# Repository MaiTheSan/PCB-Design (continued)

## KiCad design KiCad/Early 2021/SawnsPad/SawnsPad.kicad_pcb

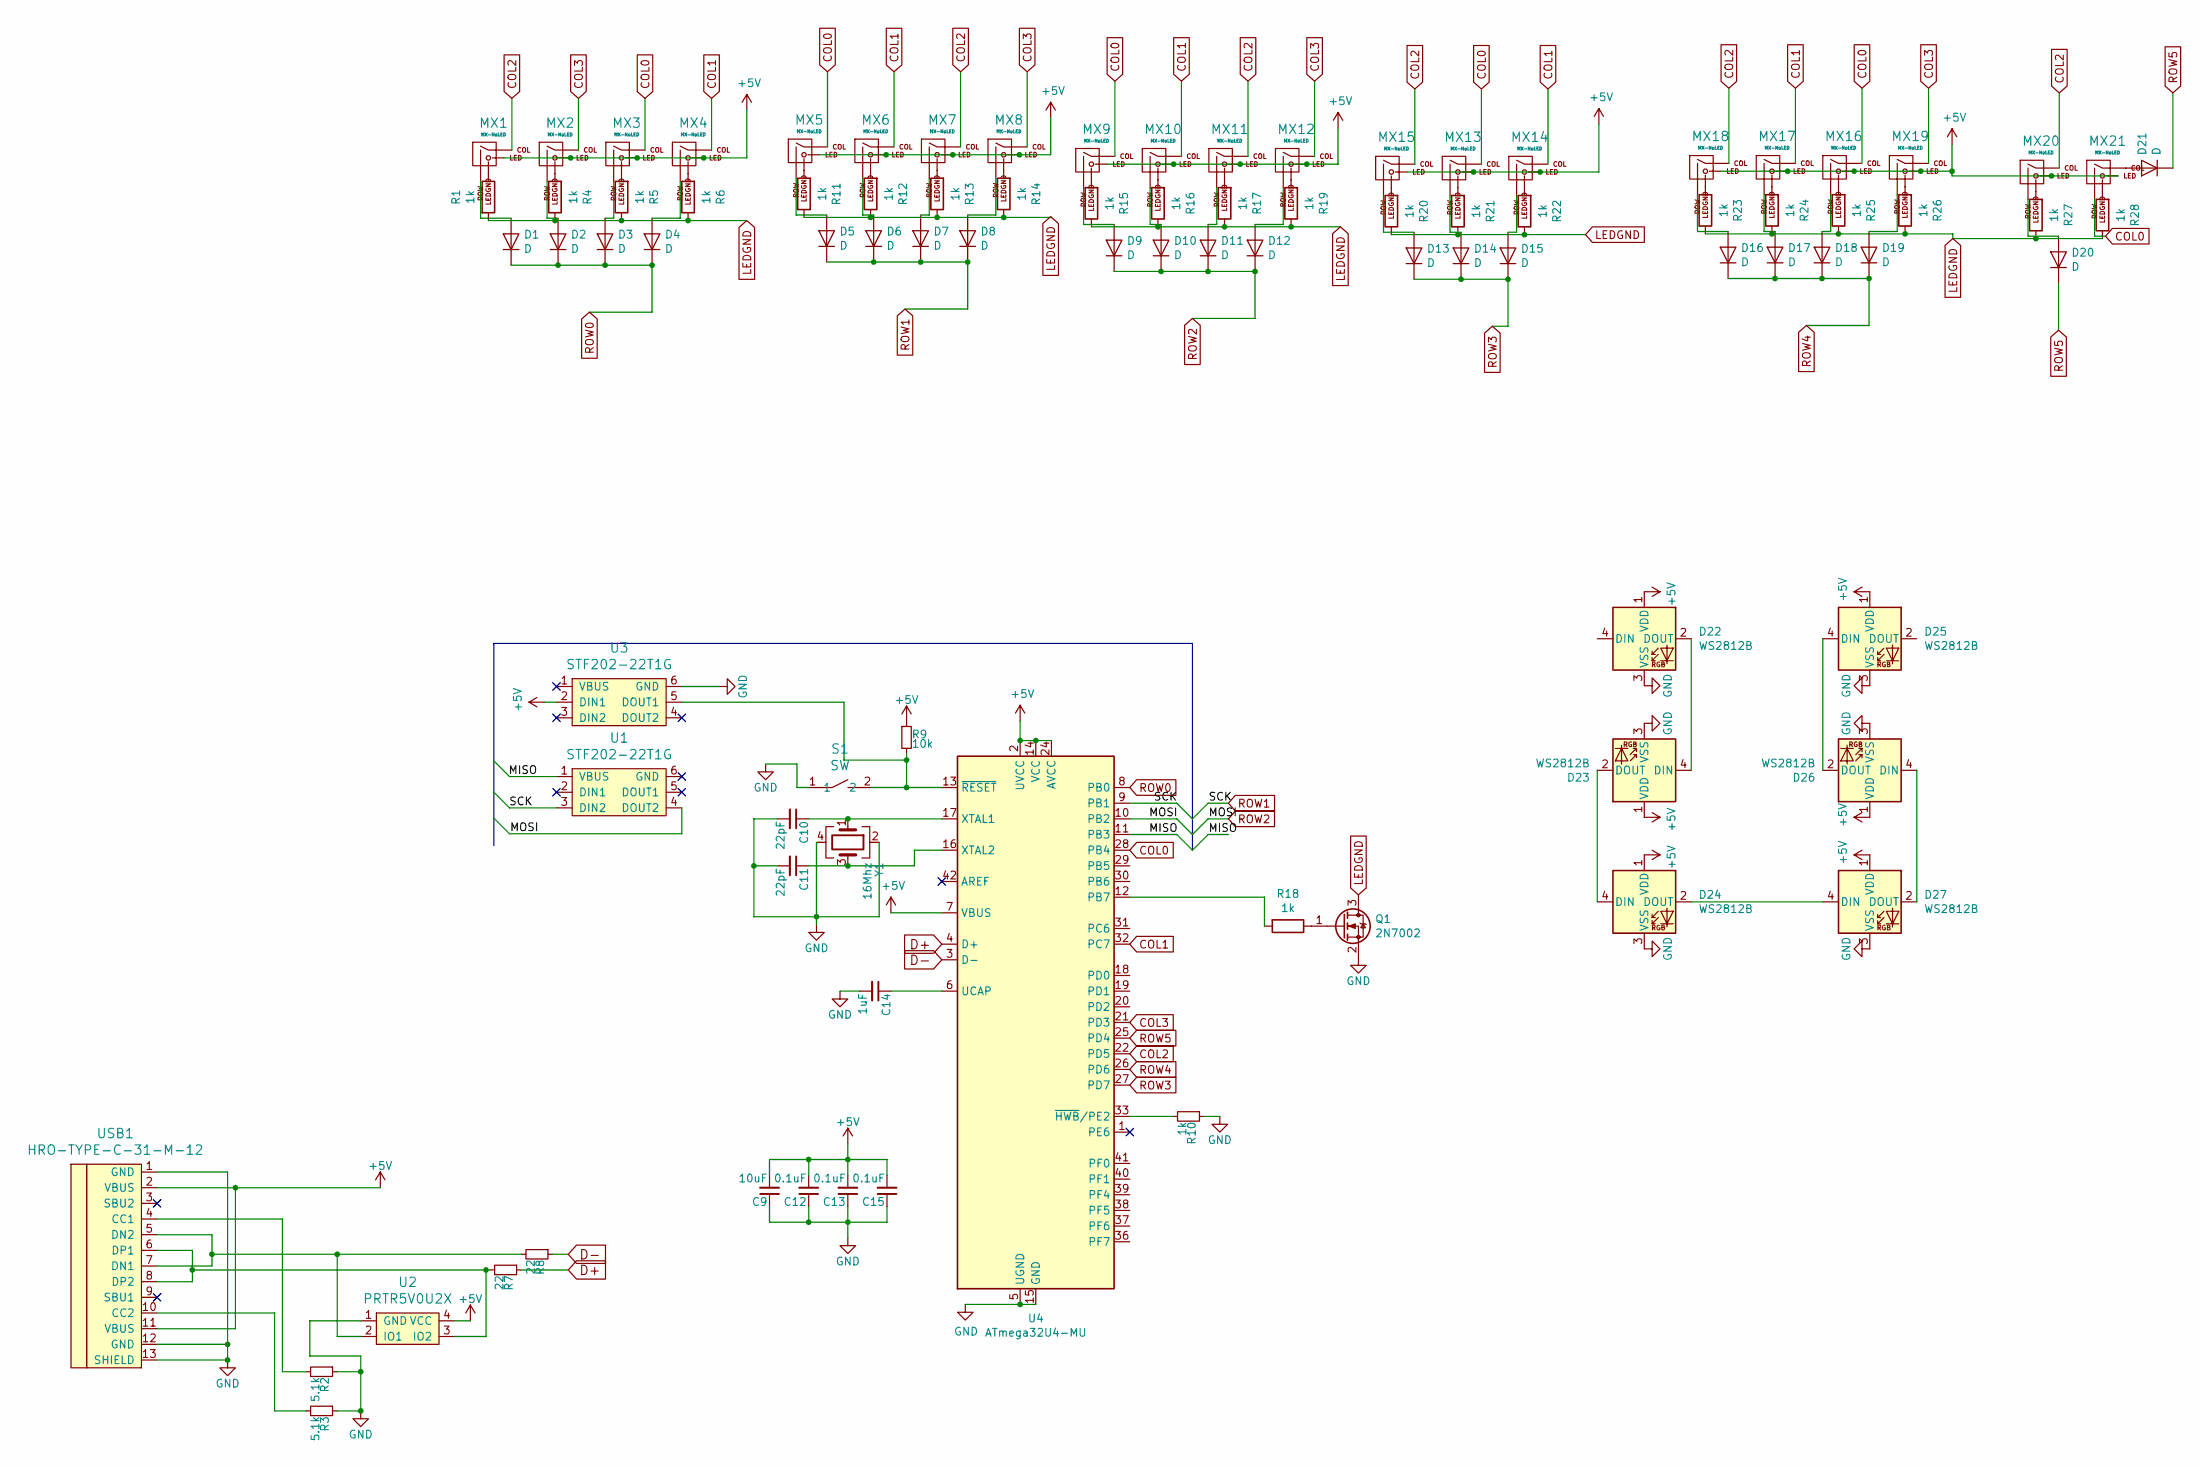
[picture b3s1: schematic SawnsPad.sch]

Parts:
C9: 10uF; SMD-0402
C10, C11: 22pF; SMD-0402
C12, C13, C15: 0.1uF; SMD-0402
C14: 1uF; SMD-0402
D1, D2, D3, D4, D5, D6, D7, D8, D9, D10, D11, D12, D13, D14, D15, D16, D17, D18, D19, D20, D21: D; D_SOD-123
D22, D23, D24, D25, D26, D27: WS2812B; LED_WS2812B_PLCC4_5.0x5.0mm_P3.2mm
MX1, MX3, MX5, MX7, MX9, MX11, MX13, MX15, MX16, MX18: MX-NoLED; MXOnly-1U-FLIPPED
MX2, MX4, MX6, MX8, MX10, MX14, MX17, MX20: MX-NoLED; MXOnly-1U
MX12: MX-NoLED; MXOnly-2U
MX19, MX21: MX-NoLED; MXOnly-2U-FLIPPED
Q1: 2N7002; SOT-23
R1, R4, R5, R6, R10, R11, R12, R13, R14, R15, R16, R17, R18, R19, R20, R21, R22, R23, R24, R25, R26, R27, R28: 1k; R_0805
R2, R3: 5.1k; R_0805
R7, R8: 22; R_0805
R9: 10k; R_0805
S1: SW; SKQG-1155865
U1, U3: STF202-22T1G; Reset_Pretty
U2: PRTR5V0U2X; SOT143B
U4: ATmega32U4-MU; QFN-44-1EP_7x7mm_P0.5mm_EP5.2x5.2mm
USB1: HRO-TYPE-C-31-M-12; HRO-TYPE-C-31-M-12-Assembly
Y1: 16Mhz; Crystal_SMD_3225-4Pin_3.2x2.5mm

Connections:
+5V: C9.2, C12.2, C13.2, C15.2, D22.1 (VDD), D23.1 (VDD), D24.1 (VDD), D25.1 (VDD), D26.1 (VDD), D27.1 (VDD), MX1.3 (LED), MX2.3 (LED), MX3.3 (LED), MX4.3 (LED), MX5.3 (LED), MX6.3 (LED), MX7.3 (LED), MX8.3 (LED), MX9.3 (LED), MX10.3 (LED), MX11.3 (LED), MX12.3 (LED), MX13.3 (LED), MX14.3 (LED), MX15.3 (LED), MX16.3 (LED), MX17.3 (LED), MX18.3 (LED), MX19.3 (LED), MX20.3 (LED), MX21.3 (LED), R9.1, U2.4 (VCC), U3.2 (DIN1), U4.2 (UVCC), U4.7 (VBUS), U4.14 (VCC), U4.24 (AVCC), U4.34 (VCC), U4.44 (AVCC), USB1.2 (VBUS), USB1.11 (VBUS)
/MISO: U1.1 (VBUS), U4.11 (PB3)
COL0: MX3.1 (COL), MX5.1 (COL), MX9.1 (COL), MX13.1 (COL), MX16.1 (COL), MX21.2 (ROW), U4.28 (PB4)
COL1: MX4.1 (COL), MX6.1 (COL), MX10.1 (COL), MX14.1 (COL), MX17.1 (COL), U4.32 (PC7)
COL2: MX1.1 (COL), MX7.1 (COL), MX11.1 (COL), MX15.1 (COL), MX18.1 (COL), MX20.1 (COL), U4.22 (PD5)
COL3: MX2.1 (COL), MX8.1 (COL), MX12.1 (COL), MX19.1 (COL), U4.21 (PD3)
D+: R7.1, U4.4 (D+)
D-: R8.1, U4.3 (D-)
GND: C9.1, C10.2, C11.2, C12.1, C13.1, C14.2, C15.1, D22.3 (VSS), D23.3 (VSS), D24.3 (VSS), D25.3 (VSS), D26.3 (VSS), D27.3 (VSS), Q1.2 (S), R2.1, R3.1, R10.1, S1.1, U2.1 (GND), U3.6 (GND), U4.5 (UGND), U4.15 (GND), U4.23 (GND), U4.35 (GND), U4.43 (GND), U4.45 (GND), USB1.1 (GND), USB1.12 (GND), USB1.13 (SHIELD), Y1.2, Y1.4
LEDGND: Q1.3 (D), R1.2, R4.1, R5.1, R6.1, R11.1, R12.1, R13.1, R14.1, R15.1, R16.1, R17.1, R19.1, R20.1, R21.1, R22.1, R23.1, R24.1, R25.1, R26.1, R27.1, R28.1
unnamed: C10.1, U4.17 (XTAL1), Y1.1
unnamed: C11.1, U4.16 (XTAL2), Y1.3
unnamed: C14.1, U4.6 (UCAP)
unnamed: D1.2 (A), MX1.2 (ROW)
unnamed: D2.2 (A), MX2.2 (ROW)
unnamed: D3.2 (A), MX3.2 (ROW)
unnamed: D4.2 (A), MX4.2 (ROW)
unnamed: D5.2 (A), MX5.2 (ROW)
unnamed: D6.2 (A), MX6.2 (ROW)
unnamed: D7.2 (A), MX7.2 (ROW)
unnamed: D8.2 (A), MX8.2 (ROW)
unnamed: D9.2 (A), MX9.2 (ROW)
unnamed: D10.2 (A), MX10.2 (ROW)
unnamed: D11.2 (A), MX11.2 (ROW)
unnamed: D12.2 (A), MX12.2 (ROW)
unnamed: D13.2 (A), MX15.2 (ROW)
unnamed: D14.2 (A), MX13.2 (ROW)
unnamed: D15.2 (A), MX14.2 (ROW)
unnamed: D16.2 (A), MX18.2 (ROW)
unnamed: D17.2 (A), MX17.2 (ROW)
unnamed: D18.2 (A), MX16.2 (ROW)
unnamed: D19.2 (A), MX19.2 (ROW)
unnamed: D20.2 (A), MX20.2 (ROW)
unnamed: D21.2 (A), MX21.1 (COL)
unnamed: D22.2 (DOUT), D23.4 (DIN)
unnamed: D23.2 (DOUT), D24.4 (DIN)
unnamed: D24.2 (DOUT), D27.4 (DIN)
unnamed: D25.4 (DIN), D26.2 (DOUT)
unnamed: D26.4 (DIN), D27.2 (DOUT)
unnamed: MX1.4 (LEDGND), R1.1
unnamed: MX2.4 (LEDGND), R4.2
unnamed: MX3.4 (LEDGND), R5.2
unnamed: MX4.4 (LEDGND), R6.2
unnamed: MX5.4 (LEDGND), R11.2
unnamed: MX6.4 (LEDGND), R12.2
unnamed: MX7.4 (LEDGND), R13.2
unnamed: MX8.4 (LEDGND), R14.2
unnamed: MX9.4 (LEDGND), R15.2
unnamed: MX10.4 (LEDGND), R16.2
unnamed: MX11.4 (LEDGND), R17.2
unnamed: MX12.4 (LEDGND), R19.2
unnamed: MX13.4 (LEDGND), R21.2
unnamed: MX14.4 (LEDGND), R22.2
unnamed: MX15.4 (LEDGND), R20.2
unnamed: MX16.4 (LEDGND), R25.2
unnamed: MX17.4 (LEDGND), R24.2
unnamed: MX18.4 (LEDGND), R23.2
unnamed: MX19.4 (LEDGND), R26.2
unnamed: MX20.4 (LEDGND), R27.2
unnamed: MX21.4 (LEDGND), R28.2
unnamed: Q1.1 (G), R18.1
unnamed: R2.2, USB1.4 (CC1)
unnamed: R3.2, USB1.10 (CC2)
unnamed: R7.2, U2.3 (IO2), USB1.6 (DP1), USB1.8 (DP2)
unnamed: R8.2, U2.2 (IO1), USB1.5 (DN2), USB1.7 (DN1)
unnamed: R9.2, S1.2, U3.5 (DOUT1), U4.13 (~RESET)
unnamed: R10.2, U4.33 (~HWB~/PE2)
unnamed: R18.2, U4.12 (PB7)
ROW0: D1.1 (K), D2.1 (K), D3.1 (K), D4.1 (K), U4.8 (PB0)
ROW1: D5.1 (K), D6.1 (K), D7.1 (K), D8.1 (K), U1.3 (DIN2), U4.9 (PB1)
ROW2: D9.1 (K), D10.1 (K), D11.1 (K), D12.1 (K), U1.4 (DOUT2), U4.10 (PB2)
ROW3: D13.1 (K), D14.1 (K), D15.1 (K), U4.27 (PD7)
ROW4: D16.1 (K), D17.1 (K), D18.1 (K), D19.1 (K), U4.26 (PD6)
ROW5: D20.1 (K), D21.1 (K), U4.25 (PD4)

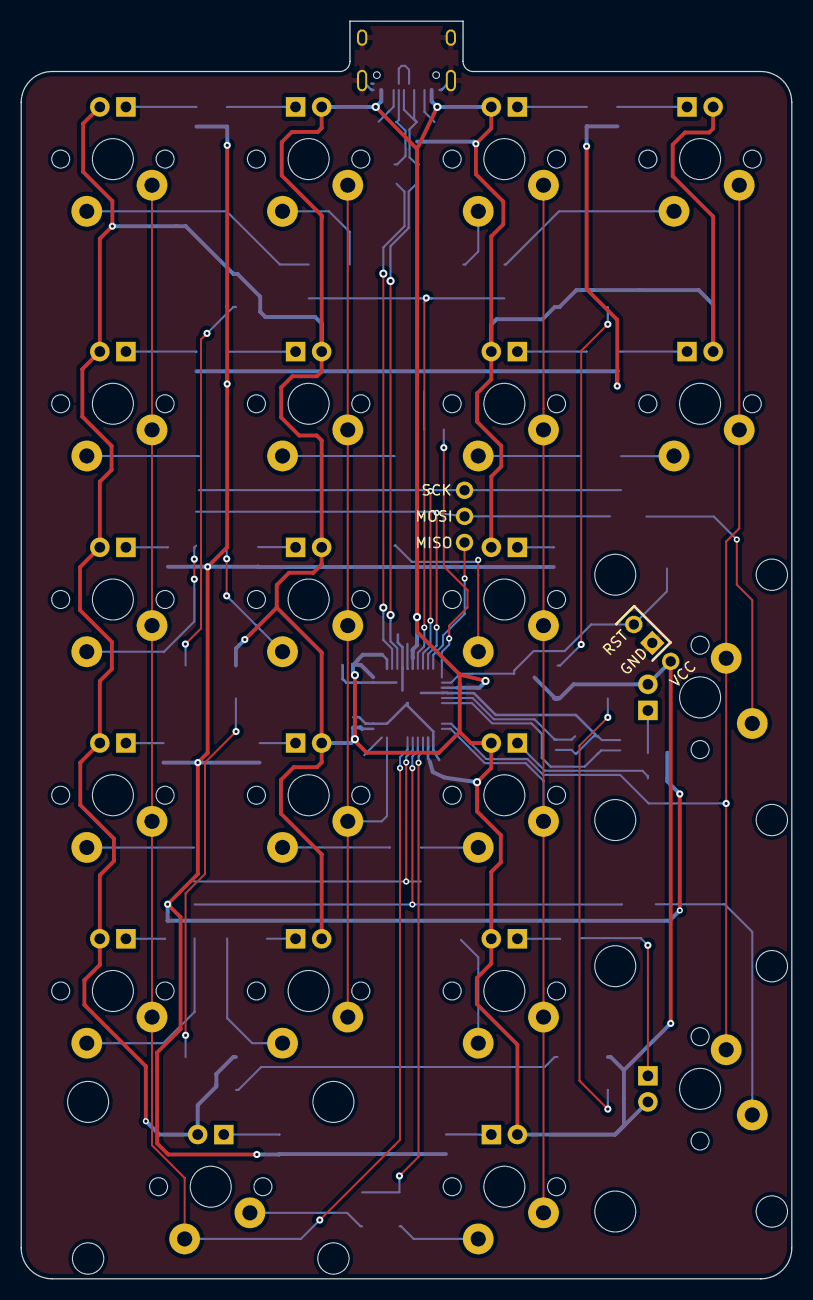
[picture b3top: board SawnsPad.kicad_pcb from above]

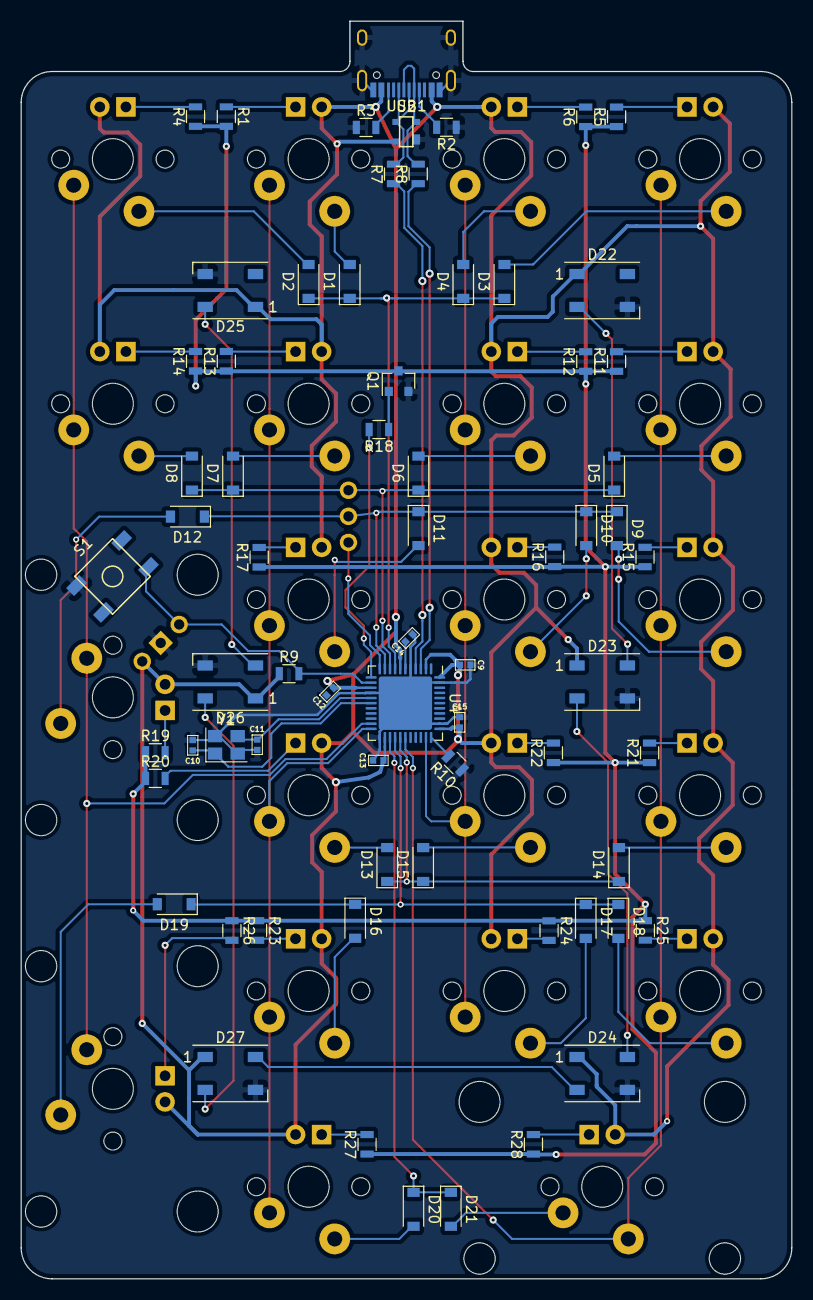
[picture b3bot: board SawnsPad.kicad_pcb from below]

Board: 2 copper layers, 75.0 x 122.4 mm, 91 parts (68 on the bottom side), 74 nets.

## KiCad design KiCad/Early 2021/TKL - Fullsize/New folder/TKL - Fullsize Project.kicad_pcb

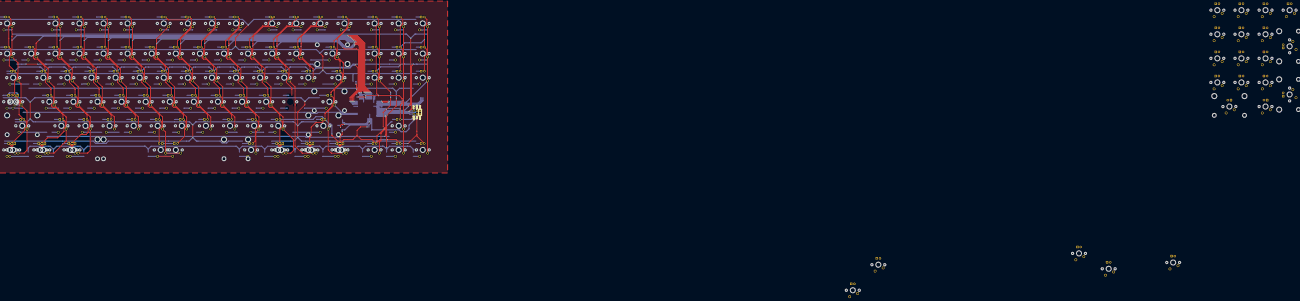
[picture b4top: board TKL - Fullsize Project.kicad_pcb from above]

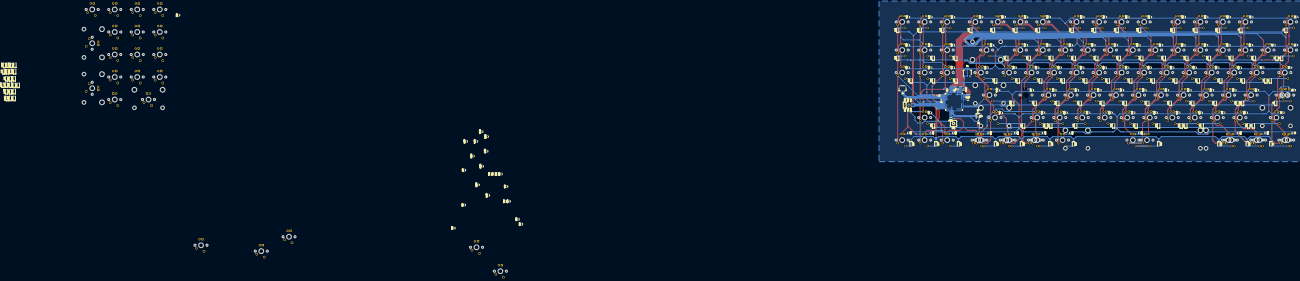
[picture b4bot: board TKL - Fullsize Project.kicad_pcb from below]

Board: 2 copper layers, 351 parts (233 on the bottom side), 257 nets.

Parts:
C2, C5: 1uF; C_0603
C3, C4: 22pF; C_0603
C6, C7, C8: 0.1uF; C_0603
D1, D2, D3, D4, D5, D6, D7, D8, D9, D10, D11, D12, D13, D14, D15, D16, D17, D18, D19, D20, D21, D22, D23, D24, D25, D26, D27, D28, D29, D30, D31, D32, D33, D34, D35, D36, D37, D38, D39, D40, D41, D42, D43, D44, D45, D46, D47, D48, D49, D50, D51, D52, D53, D54, D55, D56, D57, D58, D59, D60, D61, D62, D63, D64, D65, D66, D67, D68, D69, D70, D71, D72, D73, D74, D75, D76, D77, D78, D79, D80, D81, D82, D83, D84, D85, D86, D87, D88, D89, D90, D91, D92, D93, D94, D95, D96, D97, D98, D99, D100, D101, D102, D103, D104, D105, D106, D107, D108, D110: SOD-123; D_SOD-123-Pretty
J1: AVR-ISP-6; Reset_Pretty-Mask
J2: SM04B-SRSS-TB(LF)(SN); JST-SR-4
K_0: MX 2U; MXOnly-2U-FLIPPED
K_0x1, K_1, K_2, K_3, K_4, K_5, K_6, K_7, K_8, K_9: MX 1U; MXOnly-1U
K_': MXOnly-1U
K_*1: MX 1U; MXOnly-1U
K_+1: MX 1U; MXOnly-1U
K_+2: MX 2U; MXOnly-2U
K_-1, K_-2: MX 1U; MXOnly-1U
K_/1: MX 1U; MXOnly-1U
K_/?/1: MX 1U; MXOnly-1U
K_:;1: MX 1U; MXOnly-1U
K_<1: MX 1U; MXOnly-1U
K_>1: MX 1U; MXOnly-1U
K_A1: MX 1U; MXOnly-1U
K_B1: MX 1U; MXOnly-1U
K_BkSp1: MX 2U; MXOnly-2U-ReversedStabilizers
K_C1: MX 1U; MXOnly-1U
K_CapLk1: MX 1.25U; MXOnly-1.25U
K_CapLk2: MX 1.75U; MXOnly-1.75U-FLIPPED
K_D1: MX 1U; MXOnly-1U
K_Del1: MX 1U; MXOnly-1U-FLIPPED
K_Delete1: MX 1U; MXOnly-1U
K_Down1: MX 1U; MXOnly-1U
K_E1: MX 1U; MXOnly-1U
K_ESC1: MX 1U; MXOnly-1U
K_End1: MX 1U; MXOnly-1U
K_Enter1: MX 2.25U; MXOnly-2.25U
K_Enter2: MX 2U; MXOnly-2U
K_F1, K_F2, K_F3, K_F4, K_F5, K_F6, K_F7, K_F8, K_F9, K_F10, K_F11, K_F12, K_F13: MX 1U; MXOnly-1U
K_FN5: MX 1.25U; MXOnly-1.25U-FLIPPED
K_Fn1, K_Fn2, K_Fn3, K_Fn4: MX 1U; MXOnly-1U
K_G1: MX 1U; MXOnly-1U
K_H1: MX 1U; MXOnly-1U
K_Home1: MX 1U; MXOnly-1U
K_I1: MX 1U; MXOnly-1U
K_Ins1: MX 1U; MXOnly-1U
K_J1: MX 1U; MXOnly-1U
K_K1: MX 1U; MXOnly-1U
K_L1: MX 1U; MXOnly-1U
K_Left1: MX 1U; MXOnly-1U
K_LeftAlt1: MX 1.25U; MXOnly-1.25U
K_LeftAlt2: MX 1.5U; MXOnly-1.5U-FLIPPED
K_LeftControl1: MX 1.25U; MXOnly-1.25U
K_LeftControl2: MX 1.5U; MXOnly-1.5U-FLIPPED
K_LeftShift1: MX 2.25U; MXOnly-2.25U
K_LeftWin1: MX 1.25U; MXOnly-1.25U
K_LeftWin2: MX 1U; MXOnly-1U-FLIPPED
K_M1: MX 1U; MXOnly-1U
K_Menu1: MX 1.25U; MXOnly-1.25U-FLIPPED
K_N1: MX 1U; MXOnly-1U
K_Num1, K_Num2, K_Num3, K_Num4, K_Num5, K_Num6, K_Num7, K_Num8, K_Num9: MX 1U; MXOnly-1U
K_NumLk1: MX 1U; MXOnly-1U
K_O1: MX 1U; MXOnly-1U
K_P1: MX 1U; MXOnly-1U
K_Pause1: MX 1U; MXOnly-1U
K_PgDn1: MX 1U; MXOnly-1U
K_PgUp1: MX 1U; MXOnly-1U
K_PrtSc1: MX 1U; MXOnly-1U
K_Q1: MX 1U; MXOnly-1U
K_R1: MX 1U; MXOnly-1U
K_Right1: MX 1U; MXOnly-1U
K_RightAlt1: MX 1.25U; MXOnly-1.25U
K_RightAltx1: MX 1.5U; MXOnly-1.5U
K_RightControl1: MX 1.25U; MXOnly-1.25U-FLIPPED
K_RightFN1: MX 1.5U; MXOnly-1.5U
K_RightShift1: MX 2.75U; MXOnly-2.75U
K_Rightwinx1: MX 1U; MXOnly-1U
K_S1: MX 1U; MXOnly-1U
K_ScLk1: MX 1U; MXOnly-1U
K_Sleep1: MX 1U; MXOnly-1U
K_Space1: MX 6.25U; MXOnly-6.25U-FLIPPED
K_Space2: MX 7U; MXOnly-7U
K_T1: MX 1U; MXOnly-1U
K_Tab1: MX 1.5U; MXOnly-1.5U
K_U1: MX 1U; MXOnly-1U
K_Up1: MX 1U; MXOnly-1U
K_V1: MX 1U; MXOnly-1U
K_W1: MX 1U; MXOnly-1U
K_X1: MX 1U; MXOnly-1U
K_Y1: MX 1U; MXOnly-1U
K_Z1: MX 1U; MXOnly-1U
K_[{1: MX 1U; MXOnly-1U
K_\|1: MX 1.5U; MXOnly-1.5U
K_`1: MX 1U; MXOnly-1U
K_}]1: MX 1U; MXOnly-1U
Q1: DSS60601MZ4-13; SOT-223-3_TabPin2
R1, R2, R3, R4, R5, R6, R7, R8, R9, R10, R11, R12, R13, R14, R15, R16, R17, R18, R19, R20, R21, R22, R23, R24, R25, R26, R27, R28, R29, R30, R31, R32, R33, R34, R35, R36, R37, R38, R39, R40, R41, R42, R43, R44, R45, R46, R47, R48, R49, R50, R51, R52, R53, R54, R55, R56, R57, R58, R59, R60, R61, R62, R63, R64, R65, R66, R67, R68, R69, R70, R71, R72, R73, R74, R75, R76, R77, R78, R79, R80, R81, R82, R83, R84, R85, R86, R87, R89, R90, R91, R92, R93, R94, R95, R96, R97, R98, R99, R100, R101, R102, R103, R104, R105, R106, R107, R108, R111, R113: 1k; R_0805
R88: 300; R_0805
R109: 1.5k; R_0805
R112: 10k; R_0805
SW1: SW_Push; SKQG-1155865
U2: AT90USB1286-AU; TQFP-64_14x14mm_P0.8mm
Y1: 16MHz; Crystal_SMD_3225-4Pin_3.2x2.5mm

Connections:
+5V: C5.2, C6.2, C7.2, C8.2, J1.2, J2.1, K_0.3, K_0x1.3, K_1.3, K_2.3, K_3.3, K_4.3, K_5.3, K_6.3, K_7.3, K_8.3, K_9.3, K_*1.3, K_+1.3, K_+2.3, K_-1.3, K_-2.3, K_/1.3, K_/?/1.3, K_:;1.3, K_<1.3, K_>1.3, K_A1.3, K_B1.3, K_BkSp1.3, K_C1.3, K_CapLk1.3, K_CapLk2.3, K_D1.3, K_Del1.3, K_Delete1.3, K_Down1.3, K_E1.3, K_ESC1.3, K_End1.3, K_Enter1.3, K_Enter2.3, K_F1.3, K_F2.3, K_F3.3, K_F4.3, K_F5.3, K_F6.3, K_F7.3, K_F8.3, K_F9.3, K_F10.3, K_F11.3, K_F12.3, K_F13.3, K_FN5.3, K_Fn1.3, K_Fn2.3, K_Fn3.3, K_Fn4.3, K_G1.3, K_H1.3, K_Home1.3, K_I1.3, K_Ins1.3, K_J1.3, K_K1.3, K_L1.3, K_Left1.3, K_LeftAlt1.3, K_LeftAlt2.3, K_LeftControl1.3, K_LeftControl2.3, K_LeftShift1.3, K_LeftWin1.3, K_LeftWin2.3, K_M1.3, K_Menu1.3, K_N1.3, K_Num1.3, K_Num2.3, K_Num3.3, K_Num4.3, K_Num5.3, K_Num6.3, K_Num7.3, K_Num8.3, K_Num9.3, K_NumLk1.3, K_O1.3, K_P1.3, K_Pause1.3, K_PgDn1.3, K_PgUp1.3, K_PrtSc1.3, K_Q1.3, K_R1.3, K_Right1.3, K_RightAlt1.3, K_RightAltx1.3, K_RightControl1.3, K_RightFN1.3, K_RightShift1.3, K_Rightwinx1.3, K_S1.3, K_ScLk1.3, K_Sleep1.3, K_Space1.3, K_Space2.3, K_T1.3, K_Tab1.3, K_U1.3, K_Up1.3, K_V1.3, K_W1.3, K_X1.3, K_Y1.3, K_Z1.3, K_[{1.3, K_\|1.3, K_`1.3, K_}]1.3, R112.1, U2.3, U2.8, U2.21, U2.52, U2.64
Col0: K_CapLk1.1, K_CapLk2.1, K_ESC1.1, K_LeftControl1.1, K_LeftControl2.1, K_LeftShift1.1, K_Tab1.1, K_`1.1, U2.61
Col1: K_1.1, K_A1.1, K_LeftWin1.1, K_LeftWin2.1, K_Q1.1, K_Z1.1, U2.60
Col2: K_2.1, K_F1.1, K_LeftAlt1.1, K_LeftAlt2.1, K_S1.1, K_W1.1, K_X1.1, U2.59
Col3: K_3.1, K_C1.1, K_D1.1, K_E1.1, K_F2.1, U2.58
Col4: K_4.1, K_F3.1, K_F13.1, K_R1.1, K_V1.1, U2.57
Col5: K_5.1, K_B1.1, K_F4.1, K_G1.1, K_Space1.1, K_Space2.1, K_T1.1, U2.56
Col6: K_6.1, K_F5.1, K_H1.1, K_N1.1, K_Y1.1, U2.51
Col7: K_7.1, K_F6.1, K_J1.1, K_M1.1, K_U1.1, U2.50
Col8: K_8.1, K_<1.1, K_F7.1, K_I1.1, K_K1.1, U2.49
Col9: K_9.1, K_>1.1, K_F8.1, K_L1.1, K_O1.1, K_RightAlt1.1, U2.48
Col10: K_0x1.1, K_/?/1.1, K_:;1.1, K_F9.1, K_FN5.1, K_P1.1, K_RightFN1.1, U2.47
Col11: K_-1.1, K_F10.1, K_Menu1.1, K_Rightwinx1.1, K_[{1.1, U2.46
Col12: K_+1.1, K_F11.1, K_Sleep1.1, K_}]1.1, U2.45
Col13: K_BkSp1.1, K_Enter1.1, K_F12.1, K_RightAltx1.1, K_RightControl1.1, K_RightShift1.1, K_\|1.1, U2.36
Col14: K_Delete1.1, K_Ins1.1, K_Left1.1, K_PrtSc1.1, U2.9
Col15: K_Down1.1, K_End1.1, K_Home1.1, K_ScLk1.1, K_Up1.1, U2.1
Col16: K_Pause1.1, K_PgDn1.1, K_PgUp1.1, K_Right1.1, U2.2
Col17: K_Fn1.1, K_Num1.1, K_Num4.1, K_Num7.1, K_NumLk1.1
Col18: K_0.1, K_/1.1, K_Fn2.1, K_Num2.1, K_Num5.1, K_Num8.1
Col19: K_*1.1, K_Del1.1, K_Fn3.1, K_Num3.1, K_Num6.1, K_Num9.1
Col20: K_+2.1, K_-2.1, K_Enter2.1, K_Fn4.1
D+: J2.3, U2.5
D-: J2.2, U2.4
GND: C2.2, C3.2, C4.2, C5.1, C6.1, C7.1, C8.1, J1.6, J2.4, Q1.3, R113.2, SW1.1, U2.6, U2.22, U2.53, U2.63, Y1.2, Y1.4
LedGND: Q1.2, R1.1, R2.1, R3.1, R4.1, R5.1, R6.1, R7.1, R8.1, R9.1, R10.1, R11.1, R12.1, R13.1, R14.1, R15.1, R16.1, R17.1, R18.1, R19.1, R20.1, R21.1, R22.1, R23.1, R24.1, R25.1, R26.1, R27.1, R28.1, R29.1, R30.1, R31.1, R32.1, R33.1, R34.1, R35.1, R36.1, R37.1, R38.1, R39.1, R40.1, R41.1, R42.1, R43.1, R44.1, R45.1, R46.1, R47.1, R48.1, R49.1, R50.1, R51.1, R52.1, R53.1, R54.1, R55.1, R56.1, R57.1, R58.1, R59.1, R60.1, R61.1, R62.1, R63.1, R64.1, R65.1, R66.1, R67.1, R68.1, R69.1, R70.1, R71.1, R72.1, R73.1, R74.1, R75.1, R76.1, R77.1, R78.1, R79.1, R80.1, R81.1, R82.1, R83.1, R84.1, R85.1, R86.1, R87.1, R89.1, R90.1, R91.1, R92.1, R93.1, R94.1, R95.1, R96.1, R97.1, R98.1, R99.1, R100.1, R101.1, R102.1, R103.1, R104.1, R105.1, R106.1, R107.1, R108.1, R111.1
MISO: J1.1, U2.13
MOSI: J1.4, U2.12
unnamed: C2.1, U2.7
unnamed: D1.2, K_ESC1.2
unnamed: D2.2, K_`1.2
unnamed: D3.2, K_Tab1.2
unnamed: D4.2, K_CapLk1.2, K_CapLk2.2
unnamed: D5.2, K_LeftShift1.2
unnamed: D6.2, K_LeftControl1.2, K_LeftControl2.2
unnamed: D7.2, K_F1.2
unnamed: D8.2, K_1.2
unnamed: D9.2, K_Q1.2
unnamed: D10.2, K_A1.2
unnamed: D11.2, K_Z1.2
unnamed: D12.2, K_LeftWin1.2, K_LeftWin2.2
unnamed: D13.2, K_F2.2
unnamed: D14.2, K_2.2
unnamed: D15.2, K_W1.2
unnamed: D16.2, K_S1.2
unnamed: D17.2, K_X1.2
unnamed: D18.2, K_LeftAlt1.2, K_LeftAlt2.2
unnamed: D19.2, K_F3.2
unnamed: D20.2, K_3.2
unnamed: D21.2, K_E1.2
unnamed: D22.2, K_D1.2
unnamed: D23.2, K_C1.2
unnamed: D24.2, K_RightAltx1.2, K_RightControl1.2
unnamed: D25.2, K_F4.2
unnamed: D26.2, K_4.2
unnamed: D27.2, K_R1.2
unnamed: D28.2, K_F13.2
unnamed: D29.2, K_V1.2
unnamed: D30.2, K_F5.2
unnamed: D31.2, K_5.2
unnamed: D32.2, K_T1.2
unnamed: D33.2, K_G1.2
unnamed: D34.2, K_B1.2
unnamed: D35.2, K_Space1.2, K_Space2.2
unnamed: D36.2, K_F6.2
unnamed: D37.2, K_6.2
unnamed: D38.2, K_Y1.2
unnamed: D39.2, K_H1.2
unnamed: D40.2, K_N1.2
unnamed: D41.2, K_F7.2
unnamed: D42.2, K_7.2
unnamed: D43.2, K_U1.2
unnamed: D44.2, K_J1.2
unnamed: D45.2, K_M1.2
unnamed: D46.2, K_F8.2
unnamed: D47.2, K_8.2
unnamed: D48.2, K_I1.2
unnamed: D49.2, K_K1.2
unnamed: D50.2, K_<1.2
unnamed: D51.2, K_RightAlt1.2
unnamed: D52.2, K_F9.2
unnamed: D53.2, K_9.2
unnamed: D54.2, K_O1.2
unnamed: D55.2, K_L1.2
unnamed: D56.2, K_>1.2
unnamed: D57.2, K_FN5.2, K_RightFN1.2
unnamed: D58.2, K_F10.2
unnamed: D59.2, K_0x1.2
unnamed: D60.2, K_P1.2
unnamed: D61.2, K_:;1.2
unnamed: D62.2, K_/?/1.2
unnamed: D63.2, K_Menu1.2, K_Rightwinx1.2
unnamed: D64.2, K_F11.2
unnamed: D65.2, K_-1.2
unnamed: D66.2, K_[{1.2
unnamed: D68.2, K_RightShift1.2
unnamed: D69.2, K_F12.2
unnamed: D70.2, K_+1.2
unnamed: D71.2, K_}]1.2
unnamed: D72.2, K_Sleep1.2
unnamed: D73.2, K_BkSp1.2
unnamed: D74.2, K_\|1.2
unnamed: D75.2, K_PrtSc1.2
unnamed: D76.2, K_Ins1.2
unnamed: D77.2, K_Delete1.2
unnamed: D78.2, K_Left1.2
unnamed: D79.2, K_ScLk1.2
unnamed: D80.2, K_Home1.2
unnamed: D81.2, K_End1.2
unnamed: D82.2, K_Up1.2
unnamed: D83.2, K_Down1.2
unnamed: D84.2, K_Pause1.2
unnamed: D85.2, K_PgUp1.2
unnamed: D86.2, K_PgDn1.2
unnamed: D87.2, K_Right1.2
unnamed: D88.2, K_Fn1.2
unnamed: D89.2, K_NumLk1.2
unnamed: D90.2, K_Num7.2
unnamed: D91.2, K_Num4.2
unnamed: D92.2, K_Num1.2
unnamed: D93.2, K_0.2
unnamed: D94.2, K_Fn2.2
unnamed: D95.2, K_/1.2
unnamed: D96.2, K_Num8.2
unnamed: D97.2, K_Num5.2
unnamed: D98.2, K_Num2.2
unnamed: D99.2, K_Del1.2
unnamed: D100.2, K_Fn3.2
unnamed: D101.2, K_*1.2
unnamed: D102.2, K_Num9.2
unnamed: D103.2, K_Num6.2
unnamed: D104.2, K_Num3.2
unnamed: D105.2, K_Fn4.2
unnamed: D106.2, K_-2.2
unnamed: D107.2, K_+2.2
unnamed: D108.2, K_Enter2.2
unnamed: D110.2, K_Enter1.2
unnamed: K_0.4, R93.2
unnamed: K_0x1.4, R59.2
unnamed: K_1.4, R8.2
unnamed: K_2.4, R14.2
unnamed: K_3.4, R20.2
unnamed: K_4.4, R26.2
unnamed: K_5.4, R31.2
unnamed: K_6.4, R37.2
unnamed: K_7.4, R42.2
unnamed: K_8.4, R47.2
unnamed: K_9.4, R53.2
unnamed: K_*1.4, R101.2
unnamed: K_+1.4, R70.2
unnamed: K_+2.4, R107.2
unnamed: K_-1.4, R65.2
unnamed: K_-2.4, R106.2
unnamed: K_/1.4, R95.2
unnamed: K_/?/1.4, R62.2
unnamed: K_:;1.4, R61.2
unnamed: K_<1.4, R50.2
unnamed: K_>1.4, R56.2
unnamed: K_A1.4, R10.2
unnamed: K_B1.4, R34.2
unnamed: K_BkSp1.4, R73.2
unnamed: K_C1.4, R23.2
unnamed: K_CapLk1.4, K_CapLk2.4, R1.2
unnamed: K_D1.4, R22.2
unnamed: K_Del1.4, R99.2
unnamed: K_Delete1.4, R77.2
unnamed: K_Down1.4, R83.2
unnamed: K_E1.4, R21.2
unnamed: K_ESC1.4, R2.2
unnamed: K_End1.4, R81.2
unnamed: K_Enter1.4, R111.2
unnamed: K_Enter2.4, R108.2
unnamed: K_F1.4, R7.2
unnamed: K_F2.4, R13.2
unnamed: K_F3.4, R19.2
unnamed: K_F4.4, R25.2
unnamed: K_F5.4, R30.2
unnamed: K_F6.4, R36.2
unnamed: K_F7.4, R41.2
unnamed: K_F8.4, R46.2
unnamed: K_F9.4, R52.2
unnamed: K_F10.4, R58.2
unnamed: K_F11.4, R64.2
unnamed: K_F12.4, R69.2
unnamed: K_F13.4, R28.2
unnamed: K_FN5.4, K_RightFN1.4, R57.2
unnamed: K_Fn1.4, R89.2
unnamed: K_Fn2.4, R94.2
unnamed: K_Fn3.4, R100.2
unnamed: K_Fn4.4, R105.2
unnamed: K_G1.4, R33.2
unnamed: K_H1.4, R39.2
unnamed: K_Home1.4, R80.2
unnamed: K_I1.4, R48.2
unnamed: K_Ins1.4, R76.2
unnamed: K_J1.4, R44.2
unnamed: K_K1.4, R49.2
unnamed: K_L1.4, R55.2
unnamed: K_Left1.4, R78.2
unnamed: K_LeftAlt1.4, K_LeftAlt2.4, R18.2
unnamed: K_LeftControl1.4, K_LeftControl2.4, R6.2
unnamed: K_LeftShift1.4, R5.2
unnamed: K_LeftWin1.4, K_LeftWin2.4, R12.2
unnamed: K_M1.4, R45.2
unnamed: K_Menu1.4, K_Rightwinx1.4, R63.2
unnamed: K_N1.4, R40.2
unnamed: K_Num1.4, R92.2
unnamed: K_Num2.4, R98.2
unnamed: K_Num3.4, R104.2
unnamed: K_Num4.4, R91.2
unnamed: K_Num5.4, R97.2
unnamed: K_Num6.4, R103.2
unnamed: K_Num7.4, R90.2
unnamed: K_Num8.4, R96.2
unnamed: K_Num9.4, R102.2
unnamed: K_NumLk1.4, R88.2
unnamed: K_O1.4, R54.2
unnamed: K_P1.4, R60.2
unnamed: K_Pause1.4, R84.2
unnamed: K_PgDn1.4, R86.2
unnamed: K_PgUp1.4, R85.2
unnamed: K_PrtSc1.4, R75.2
unnamed: K_Q1.4, R9.2
unnamed: K_R1.4, R27.2
unnamed: K_Right1.4, R87.2
unnamed: K_RightAlt1.4, R51.2
unnamed: K_RightAltx1.4, K_RightControl1.4, R24.2
unnamed: K_RightShift1.4, R68.2
unnamed: K_S1.4, R16.2
unnamed: K_ScLk1.4, R79.2
unnamed: K_Sleep1.4, R72.2
unnamed: K_Space1.4, K_Space2.4, R35.2
unnamed: K_T1.4, R32.2
unnamed: K_Tab1.4, R4.2
unnamed: K_U1.4, R43.2
unnamed: K_Up1.4, R82.2
unnamed: K_V1.4, R29.2
unnamed: K_W1.4, R15.2
unnamed: K_X1.4, R17.2
unnamed: K_Y1.4, R38.2
unnamed: K_Z1.4, R11.2
unnamed: K_[{1.4, R66.2
unnamed: K_\|1.4, R74.2
unnamed: K_`1.4, R3.2
unnamed: K_}]1.4, R71.2
unnamed: Q1.1, R109.1
unnamed: R109.2, U2.55
unnamed: R113.1, U2.43
RESET: J1.5, R112.2, SW1.2, U2.20
Row0: D1.1, D7.1, D13.1, D19.1, D25.1, D30.1, D36.1, D41.1, D46.1, D52.1, D58.1, D64.1, D69.1, D75.1, D79.1, D84.1, D88.1, D94.1, D100.1, D105.1, U2.10
Row1: D2.1, D8.1, D14.1, D20.1, D26.1, D31.1, D37.1, D42.1, D47.1, D53.1, D59.1, D65.1, D70.1, D73.1, D76.1, D80.1, D85.1, D89.1, D95.1, D101.1, D106.1, J1.3, U2.11
Row2: D3.1, D9.1, D15.1, D21.1, D27.1, D32.1, D38.1, D43.1, D48.1, D54.1, D60.1, D66.1, D71.1, D74.1, D77.1, D81.1, D86.1, D90.1, D96.1, D102.1, U2.14
Row3: D4.1, D10.1, D16.1, D22.1, D28.1, D33.1, D39.1, D44.1, D49.1, D55.1, D61.1, D67.1, D72.1, D91.1, D97.1, D103.1, D107.1, D110.1, U2.35
Row4: D5.1, D11.1, D17.1, D23.1, D29.1, D34.1, D40.1, D45.1, D50.1, D56.1, D62.1, D68.1, D82.1, D92.1, D98.1, D104.1, U2.16
Row5: D6.1, D12.1, D18.1, D24.1, D35.1, D51.1, D57.1, D63.1, D78.1, D83.1, D87.1, D93.1, D99.1, D108.1, U2.15
XTAL1: C3.1, U2.24, Y1.1
XTAL2: C4.1, U2.23, Y1.3
